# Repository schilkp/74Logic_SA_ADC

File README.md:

# SA-ADC
### Philipp Schilk
A discrete Successive-Approximation ADC built purely from 74-series gates.

Built to understand SA-ADCs, and serve as a demonstration unit.

## Status
Finished. 

## Specifications
| Specification  | Value  |
| :------------ | ------------: |
| Resolution  | 8-bit  |
| Sample Rate  |  1Hz - 90Hz |
| Input Voltage Range | 0-5V |
| Input | Single-ended|
| Input Source | Included Potentiometer or External Input |
| Supply Voltage | 9-12Vdc |
| Output | 8-bit parallel |

As this is a demonstration unit only really meant for DC inputs, no Sample-&-Hold
stage is included.

## Successive Approximation Architecture

This Project uses the classic DAC-based Successive Approximation Architecture [Wikipedia](https://en.wikipedia.org/wiki/Successive_approximation_ADC "DAC-based Successive Approxmation Architecture").

It is essentially an analog implementation of a binary-search algorithm. The ADC first sets 
it's DAC to 2.5V (Vref/2), and uses an analog comparator to determine if the applied input voltage is 
higher or lower than the generated voltage. Depending on the comparator's output the DAC voltage is 
then repeatedly refined to determine each bit of the conversion-result successively.

Here are two example conversions, with Vin = 2V and Vin = 0V:

The steps of the conversion are show in the State-Machine outputs/LEDs:

|  LED  | Description |
| ------------ | ------------ |
| R | SAR (Successive Approximation Register) bits 6-1 are reset |
| 7 | Bit 7 is tested and latched if set. |
| 6 | Bit 6 is tested and latched if set. |
| ... | ... |
| 0 | Bit 0 is tested. Bit 7-1 are latched into the output from the SAR , and bit 0 is latched from the comparator |

*A note on clocks/timing:*
The state machine/shift-register is clocked on the falling edge, while the SAR (Successive Approximation Register) and the output register are 
latched on the rising edge. Due to this, all signals (including the DAC and hence the
comparator output) are setup on the falling edge of the clock by the state machine, and have until the 
rising edge of the clock to stabilize and be latched into the different registers.

## Repo Overview

See [Github Releases]() for Gerbers, Interactive BOM, etc.

**Doc/**  
	Documentation  

**KiCad/**  
	KiCad Project Files (Schematic and PCB).  

**Logisim/**  
	Visual Logic Simulation.  
	Download LogiSim at [cburch.com](http://www.cburch.com/logisim/).

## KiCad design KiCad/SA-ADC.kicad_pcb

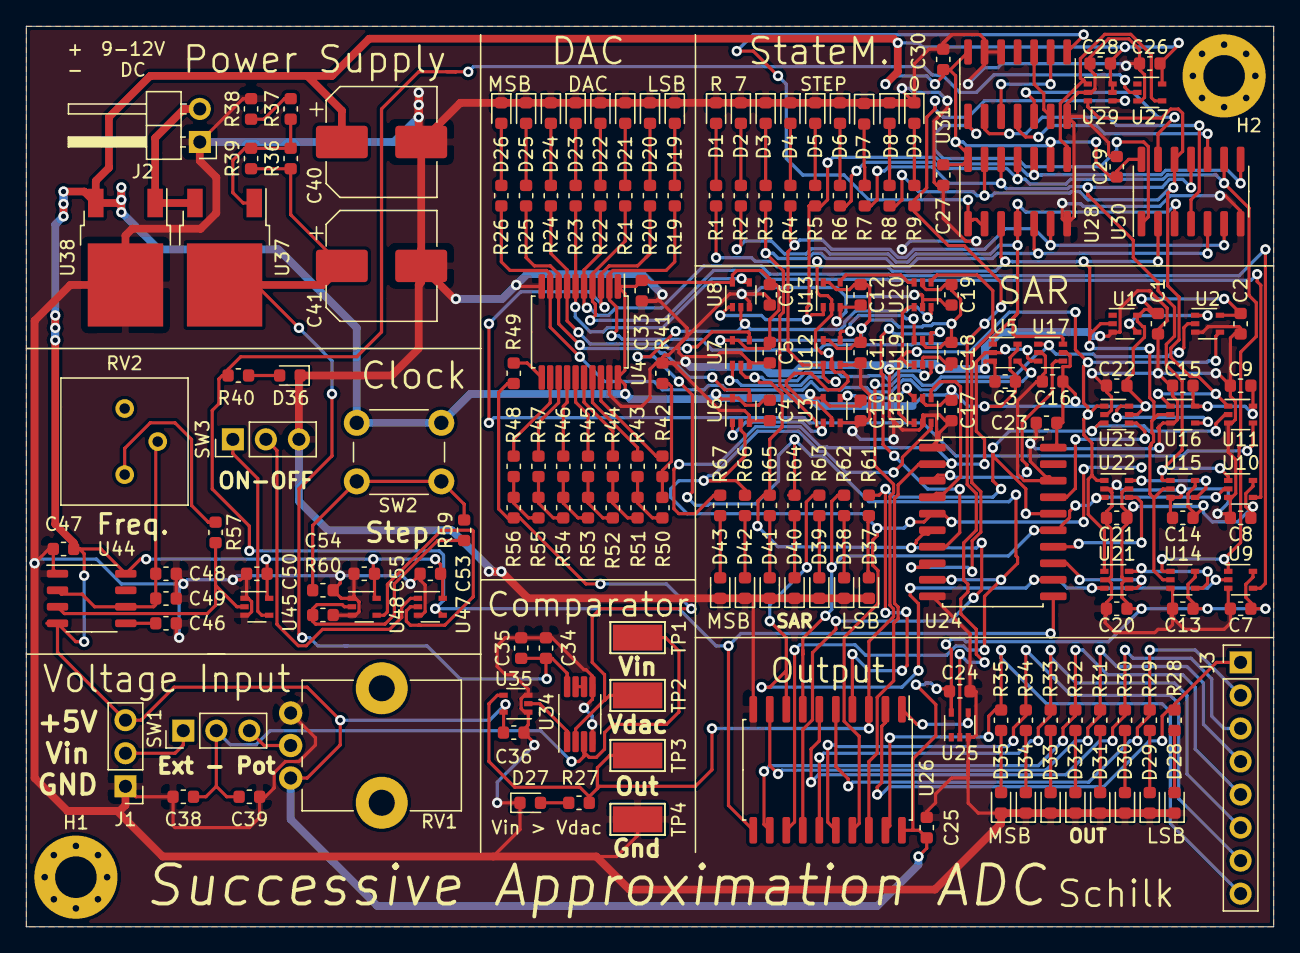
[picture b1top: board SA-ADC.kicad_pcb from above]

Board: 2 copper layers, 95.9 x 69.2 mm, 190 parts (0 on the bottom side), 127 nets.

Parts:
C1, C2, C3, C4, C5, C6, C7, C8, C9, C10, C11, C12, C13, C14, C15, C16, C17, C18, C19, C20, C21, C22, C23, C24, C25, C26, C27, C28, C29, C30, C33, C34, C36, C46, C47, C48, C50, C53, C55: 0u1; C_0603_1608Metric
C35, C38, C39, C49: DNS; C_0603_1608Metric
C40, C41: 100u; CP_Elec_8x6.5
C54: TBD; C_0603_1608Metric
D1, D2, D3, D4, D5, D6, D7, D8, D9, D19, D20, D21, D22, D23, D24, D25, D26, D27, D28, D29, D30, D31, D32, D33, D34, D35, D36, D37, D38, D39, D40, D41, D42, D43: LED; LED_0603_1608Metric
H1, H2: MountingHole; MountingHole_3.2mm_M3_Pad_Via
J1: Vin; PinHeader_1x03_P2.54mm_Vertical
J2: Power; PinHeader_1x02_P2.54mm_Horizontal
J3: Out; PinHeader_1x08_P2.54mm_Vertical
R1, R2, R3, R4, R5, R6, R7, R8, R9, R19, R20, R21, R22, R23, R24, R25, R26, R27, R28, R29, R30, R31, R32, R33, R34, R35, R40, R61, R62, R63, R64, R65, R66, R67: rled; R_0603_1608Metric
R36: 270R; R_0603_1608Metric
R37: 1K; R_0603_1608Metric
R38: 100R; R_0603_1608Metric
R39: DNS; R_0603_1608Metric
R41, R42, R43, R44, R45, R46, R47, R48, R49: 20K; R_0603_1608Metric
R50, R51, R52, R53, R54, R55, R56: 10K; R_0603_1608Metric
R57: 5K6; R_0603_1608Metric
R59, R60: TBD; R_0603_1608Metric
RV1: 10K; Potentiometer_Alps_RK09K_Single_Vertical
RV2: 1Meg; Potentiometer_Bourns_3386P_Vertical
SW1, SW3: SW_Push_SPDT; PinHeader_1x03_P2.54mm_Vertical
SW2: SW_Push; SW_PUSH_6mm
TP1: Vin; TestPoint_Keystone_5019_Minature
TP2: Vdac; TestPoint_Keystone_5019_Minature
TP3: CompOut; TestPoint_Keystone_5019_Minature
TP4: GND; TestPoint_Keystone_5019_Minature
U1, U25, U27: 74LVC1G04; SOT-353_SC-70-5
U2: 74LVC1G08; SOT-353_SC-70-5
U3, U5, U6, U7, U8, U9, U10, U11, U12, U13, U14, U15, U16, U47: 74LVC1G32; SOT-353_SC-70-5
U4: 74HC245; SSOP-20_5.3x7.2mm_P0.65mm
U17, U18, U19, U20, U21, U22, U23: 74LVC1G157; SOT-363_SC-70-6
U24, U26: 74LS377; SOIC-20W_7.5x12.8mm_P1.27mm
U28: 74HC164; SOIC-14_3.9x8.7mm_P1.27mm
U29: 74LVC1G175; SOT-363_SC-70-6
U30: 74HC02; SOIC-14_3.9x8.7mm_P1.27mm
U31: 74HC08; SOIC-14_3.9x8.7mm_P1.27mm
U34: LM358; MSOP-8_3x3mm_P0.65mm
U35, U45, U48: 74LVC1G125; SOT-353_SC-70-5
U37: LM317L_TO92; TO-252-2
U38: L7805; TO-252-2
U44: LM555; SOP-8_3.9x4.9mm_P1.27mm

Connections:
+5V: C1.1, C2.2, C3.2, C4.2, C5.2, C6.2, C7.2, C8.2, C9.2, C10.2, C11.2, C12.2, C13.2, C14.2, C15.2, C16.2, C17.2, C18.2, C19.2, C20.2, C21.2, C22.2, C23.2, C24.1, C25.2, C26.1, C27.1, C28.1, C29.1, C30.1, C33.2, C36.2, C40.1, C47.2, C50.2, C53.2, C55.2, J1.3, RV1.1, SW2.1, U1.5, U2.5, U3.5, U4.1, U4.20, U5.5, U6.5, U7.5, U8.5, U9.5, U10.5, U11.5, U12.5, U13.5, U14.5, U15.5, U16.5, U17.5, U18.5, U19.5, U20.5, U21.5, U22.5, U23.5, U24.20, U25.5, U26.20, U27.5, U28.9, U28.14, U29.5, U29.6, U30.14, U31.14, U35.5, U38.3, U44.4, U44.8, U45.5, U47.5, U48.5
/Analog/COMP_OUT: R27.2, TP3.1, U2.2, U17.1, U26.3, U35.4
/Analog/D0: R9.2, R19.2, U4.2, U25.2, U29.4
/Analog/D1: R20.2, U4.3, U11.4
/Analog/D2: R21.2, U4.4, U10.4
/Analog/D3: R22.2, U4.5, U9.4
/Analog/D4: R23.2, U4.6, U8.4
/Analog/D5: R24.2, U4.7, U7.4
/Analog/D6: R25.2, U4.8, U6.4
/Analog/D7: R26.2, U4.9, U5.4
/Analog/DAC/D0: R42.2, U4.18
/Analog/DAC/D1: R43.2, U4.17
/Analog/DAC/D2: R44.2, U4.16
/Analog/DAC/D3: R45.2, U4.15
/Analog/DAC/D4: R46.2, U4.14
/Analog/DAC/D5: R47.2, U4.13
/Analog/DAC/D6: R48.2, U4.12
/Analog/DAC/D7: R49.2, U4.11
/Analog/DAC/Vdac: R49.1, R56.1, TP2.1, U34.2
/Clock/CLK: R40.2, U24.11, U26.11, U27.2, U47.4
/Input/VIN: C38.1, C39.1, SW1.2, TP1.1, U34.3
/Output/OUT_1: R61.2, U11.2, U23.3, U24.16, U26.4
/Output/OUT_2: R62.2, U10.2, U22.3, U24.15, U26.7
/Output/OUT_3: R63.2, U9.2, U21.3, U24.12, U26.8
/Output/OUT_4: R64.2, U8.2, U20.3, U24.9, U26.13
/Output/OUT_5: R65.2, U7.2, U19.3, U24.6, U26.14
/Output/OUT_6: R66.2, U6.2, U18.3, U24.5, U26.17
/Output/OUT_7: R67.2, U5.2, U17.3, U24.2, U26.18
/SA-Register.sch/D: U2.4, U18.1, U19.1, U20.1, U21.1, U22.1, U23.1
/SA-Register.sch/STATE1: R8.2, U11.1, U16.1, U28.13, U29.3, U30.12
/SA-Register.sch/STATE2: R7.2, U10.1, U15.1, U28.12, U30.11
/SA-Register.sch/STATE3: R6.2, U9.1, U14.1, U28.11, U30.9
/SA-Register.sch/STATE4: R5.2, U8.1, U13.1, U28.10, U30.8
/SA-Register.sch/STATE5: R4.2, U7.1, U12.1, U28.6, U30.6
/SA-Register.sch/STATE6: R3.2, U3.1, U6.1, U28.5, U30.5
/SA-Register.sch/STATE7: R2.2, U5.1, U17.6, U28.4, U30.3
/SA-Register.sch/STATE_RST: R1.2, U1.2, U3.2, U12.2, U13.2, U14.2, U15.2, U16.2, U28.3, U30.2
/StateMaschine.sch/C_IN: U28.1, U28.2, U31.8
GND: C1.2, C2.1, C3.1, C4.1, C5.1, C6.1, C7.1, C8.1, C9.1, C10.1, C11.1, C12.1, C13.1, C14.1, C15.1, C16.1, C17.1, C18.1, C19.1, C20.1, C21.1, C22.1, C23.1, C24.2, C25.1, C26.2, C27.2, C28.2, C29.2, C30.2, C33.1, C34.2, C35.2, C36.1, C38.2, C39.2, C40.2, C41.2, C46.1, C47.1, C48.1, C49.1, C50.1, C53.1, C54.2, C55.1, D1.1, D2.1, D3.1, D4.1, D5.1, D6.1, D7.1, D8.1, D9.1, D19.1, D20.1, D21.1, D22.1, D23.1, D24.1, D25.1, D26.1, D27.1, D28.1, D29.1, D30.1, D31.1, D32.1, D33.1, D34.1, D35.1, D36.1, D37.1, D38.1, D39.1, D40.1, D41.1, D42.1, D43.1, J1.1, J2.1, R38.2, R41.2, R60.2, RV1.3, SW3.3, TP4.1, U1.3, U2.3, U3.3, U4.10, U4.19, U5.3, U6.3, U7.3, U8.3, U9.3, U10.3, U11.3, U12.3, U13.3, U14.3, U15.3, U16.3, U17.2, U18.2, U19.2, U20.2, U21.2, U22.2, U23.2, U24.1, U24.10, U24.18, U25.3, U26.10, U27.3, U28.7, U29.2, U30.7, U31.7, U31.12, U31.13, U34.4, U34.5, U35.1, U35.3, U38.2, U44.1, U45.1, U45.3, U47.3, U48.1, U48.3
unnamed: C46.2, U44.5
unnamed: C48.2, C49.2, RV2.2, U44.2, U44.6
unnamed: C54.1, R59.1, U48.2
unnamed: D1.2, R1.1
unnamed: D2.2, R2.1
unnamed: D3.2, R3.1
unnamed: D4.2, R4.1
unnamed: D5.2, R5.1
unnamed: D6.2, R6.1
unnamed: D7.2, R7.1
unnamed: D8.2, R8.1
unnamed: D9.2, R9.1
unnamed: D19.2, R19.1
unnamed: D20.2, R20.1
unnamed: D21.2, R21.1
unnamed: D22.2, R22.1
unnamed: D23.2, R23.1
unnamed: D24.2, R24.1
unnamed: D25.2, R25.1
unnamed: D26.2, R26.1
unnamed: D27.2, R27.1
unnamed: D28.2, R28.1
unnamed: D29.2, R29.1
unnamed: D30.2, R30.1
unnamed: D31.2, R31.1
unnamed: D32.2, R32.1
unnamed: D33.2, R33.1
unnamed: D34.2, R34.1
unnamed: D35.2, R35.1
unnamed: D36.2, R40.1
unnamed: D37.2, R61.1
unnamed: D38.2, R62.1
unnamed: D39.2, R63.1
unnamed: D40.2, R64.1
unnamed: D41.2, R65.1
unnamed: D42.2, R66.1
unnamed: D43.2, R67.1
unnamed: J1.2, SW1.1
unnamed: J2.2, U37.3, U38.1
unnamed: J3.1, R28.2, U26.2
unnamed: J3.2, R29.2, U26.5
unnamed: J3.3, R30.2, U26.6
unnamed: J3.4, R31.2, U26.9
unnamed: J3.5, R32.2, U26.12
unnamed: J3.6, R33.2, U26.15
unnamed: J3.7, R34.2, U26.16
unnamed: J3.8, R35.2, U26.19
unnamed: R36.2, R37.1, R39.2, U37.1
unnamed: R37.2, R38.1
unnamed: R41.1, R42.1, R50.1
unnamed: R43.1, R50.2, R51.2
unnamed: R44.1, R51.1, R52.2
unnamed: R45.1, R52.1, R53.2
unnamed: R46.1, R53.1, R54.2
unnamed: R47.1, R54.1, R55.2
unnamed: R48.1, R55.1, R56.2
unnamed: R57.1, RV2.1
unnamed: R57.2, U44.3, U45.2
unnamed: R59.2, R60.1, SW2.2
unnamed: RV1.2, SW1.3
unnamed: SW3.1, U45.4
unnamed: SW3.2, U47.1
unnamed: U1.4, U2.1
unnamed: U12.4, U19.6
unnamed: U13.4, U20.6
unnamed: U14.4, U21.6
unnamed: U15.4, U22.6
unnamed: U16.4, U23.6
unnamed: U17.4, U24.3
unnamed: U18.4, U24.4
unnamed: U3.4, U18.6
unnamed: U19.4, U24.7
unnamed: U20.4, U24.8
unnamed: U21.4, U24.13
unnamed: U22.4, U24.14
unnamed: U23.4, U24.17
unnamed: U25.4, U26.1
unnamed: U27.4, U28.8, U29.1
unnamed: U30.1, U31.1
unnamed: U30.4, U31.2
unnamed: U30.10, U31.4
unnamed: U30.13, U31.5
unnamed: U31.3, U31.9
unnamed: U31.6, U31.10
unnamed: U34.1, U35.2
unnamed: U34.6, U34.7
unnamed: U47.2, U48.4
VDDA: C34.1, C35.1, C41.1, R36.1, R39.1, U34.8, U37.2

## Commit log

2020-02-13 v0.0 - Initial Commit
    Initial Commit. State of Project for production of v0.0.
2020-02-13 fixed version numbering in schematic/board project files & pdf
2020-02-13 Added v0.0 Gerbers
2020-02-14 Added Render of v0.0 PCB
2020-02-14 Created README content.
2020-02-14 Updated README.md with Projet Status
2020-02-14 Added MIT License
2020-02-14 Added Logisim Simulation
2020-02-14 Updated README.md with Overview Section
2020-04-09 fixed small typo
2020-04-09 Removed version nums
2020-04-09 Fixed netlist-conformity due to renamed schematic sheet.
2020-04-09 Fixed missing grounding on de-bounce cap
2020-04-09 fixed small typos
2020-06-02 Greatly simplified Circuit in Simulation
2020-06-02 Schematic Update First Draft, ERC Passed
2020-06-03 First part placement
2020-06-03 First Layout (All Connected, passes DRC)
2020-06-08 Added GND test-point
2020-06-11 Updated Clock Component Values
2020-06-11 Fixed State Numbering/Wiring Order
2020-06-11 Generated Production Files
2020-06-11 Updated Documentation
2020-06-11 small readme fix
2020-07-08 PCB v0.2.
2020-07-08 Updated changelog
2020-08-26 v0.3 Changed to Schmitt-Trigger ICs Added pull-down resistor to Clock Enable
2020-08-26 Added PCB picture
2020-08-26 Added PCB picture to README
2020-08-27 README updates
2020-10-31 Ignore HTML in language stats
2020-10-31 Slight README updates
2020-11-01 Ignore HTML, really now.
2020-11-01 Added Example Traces
2021-05-24 Show KiCad in github language stats.
2021-07-28 Small readme fix.
2021-09-05 Small README change.
